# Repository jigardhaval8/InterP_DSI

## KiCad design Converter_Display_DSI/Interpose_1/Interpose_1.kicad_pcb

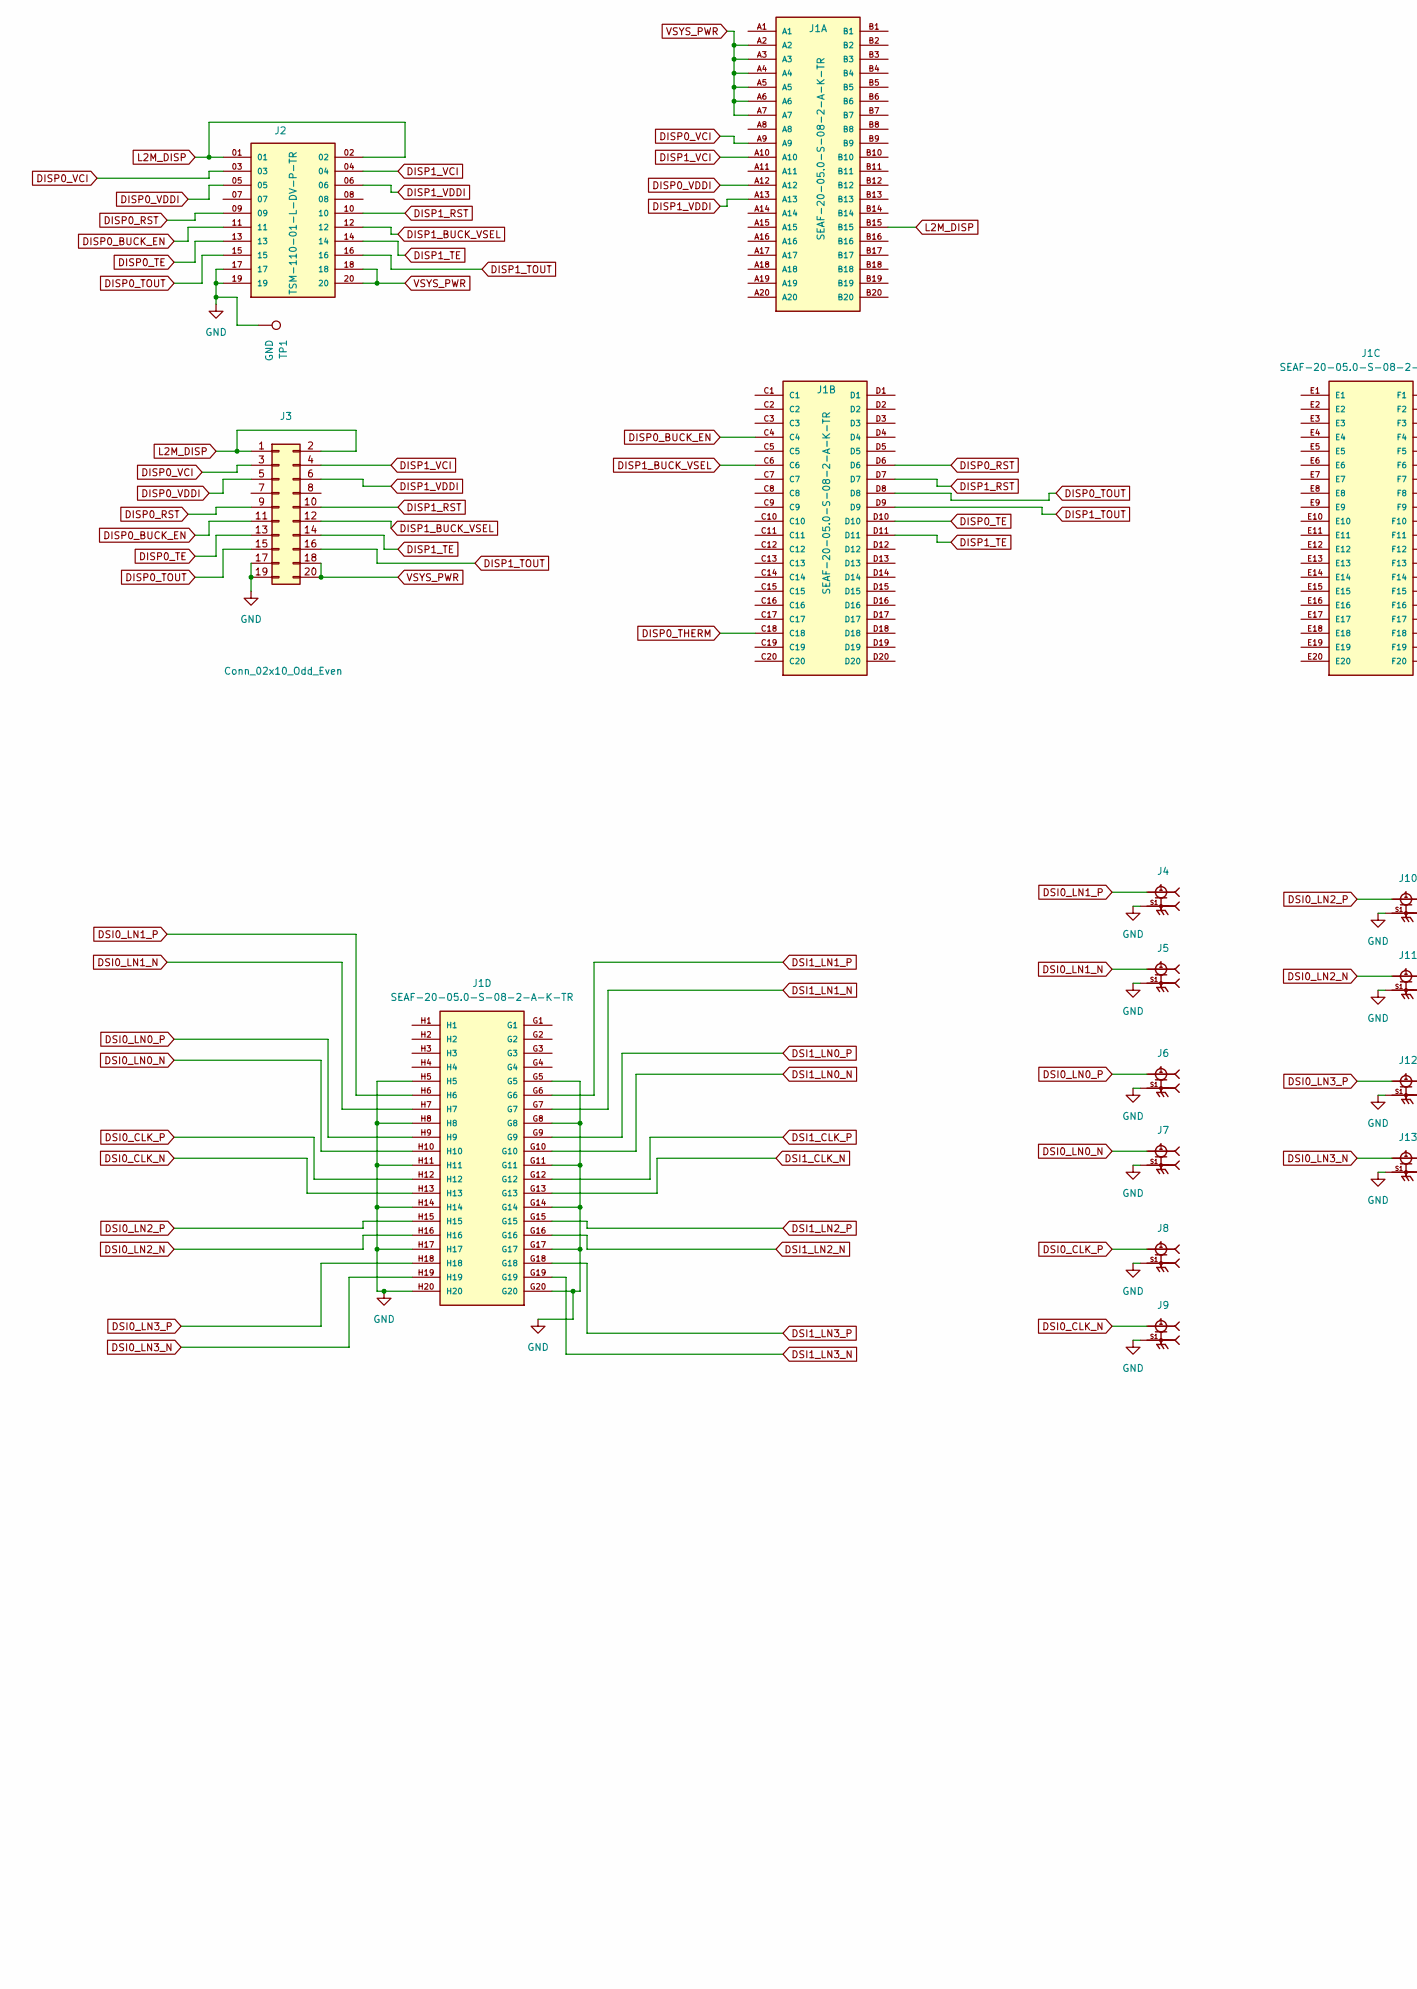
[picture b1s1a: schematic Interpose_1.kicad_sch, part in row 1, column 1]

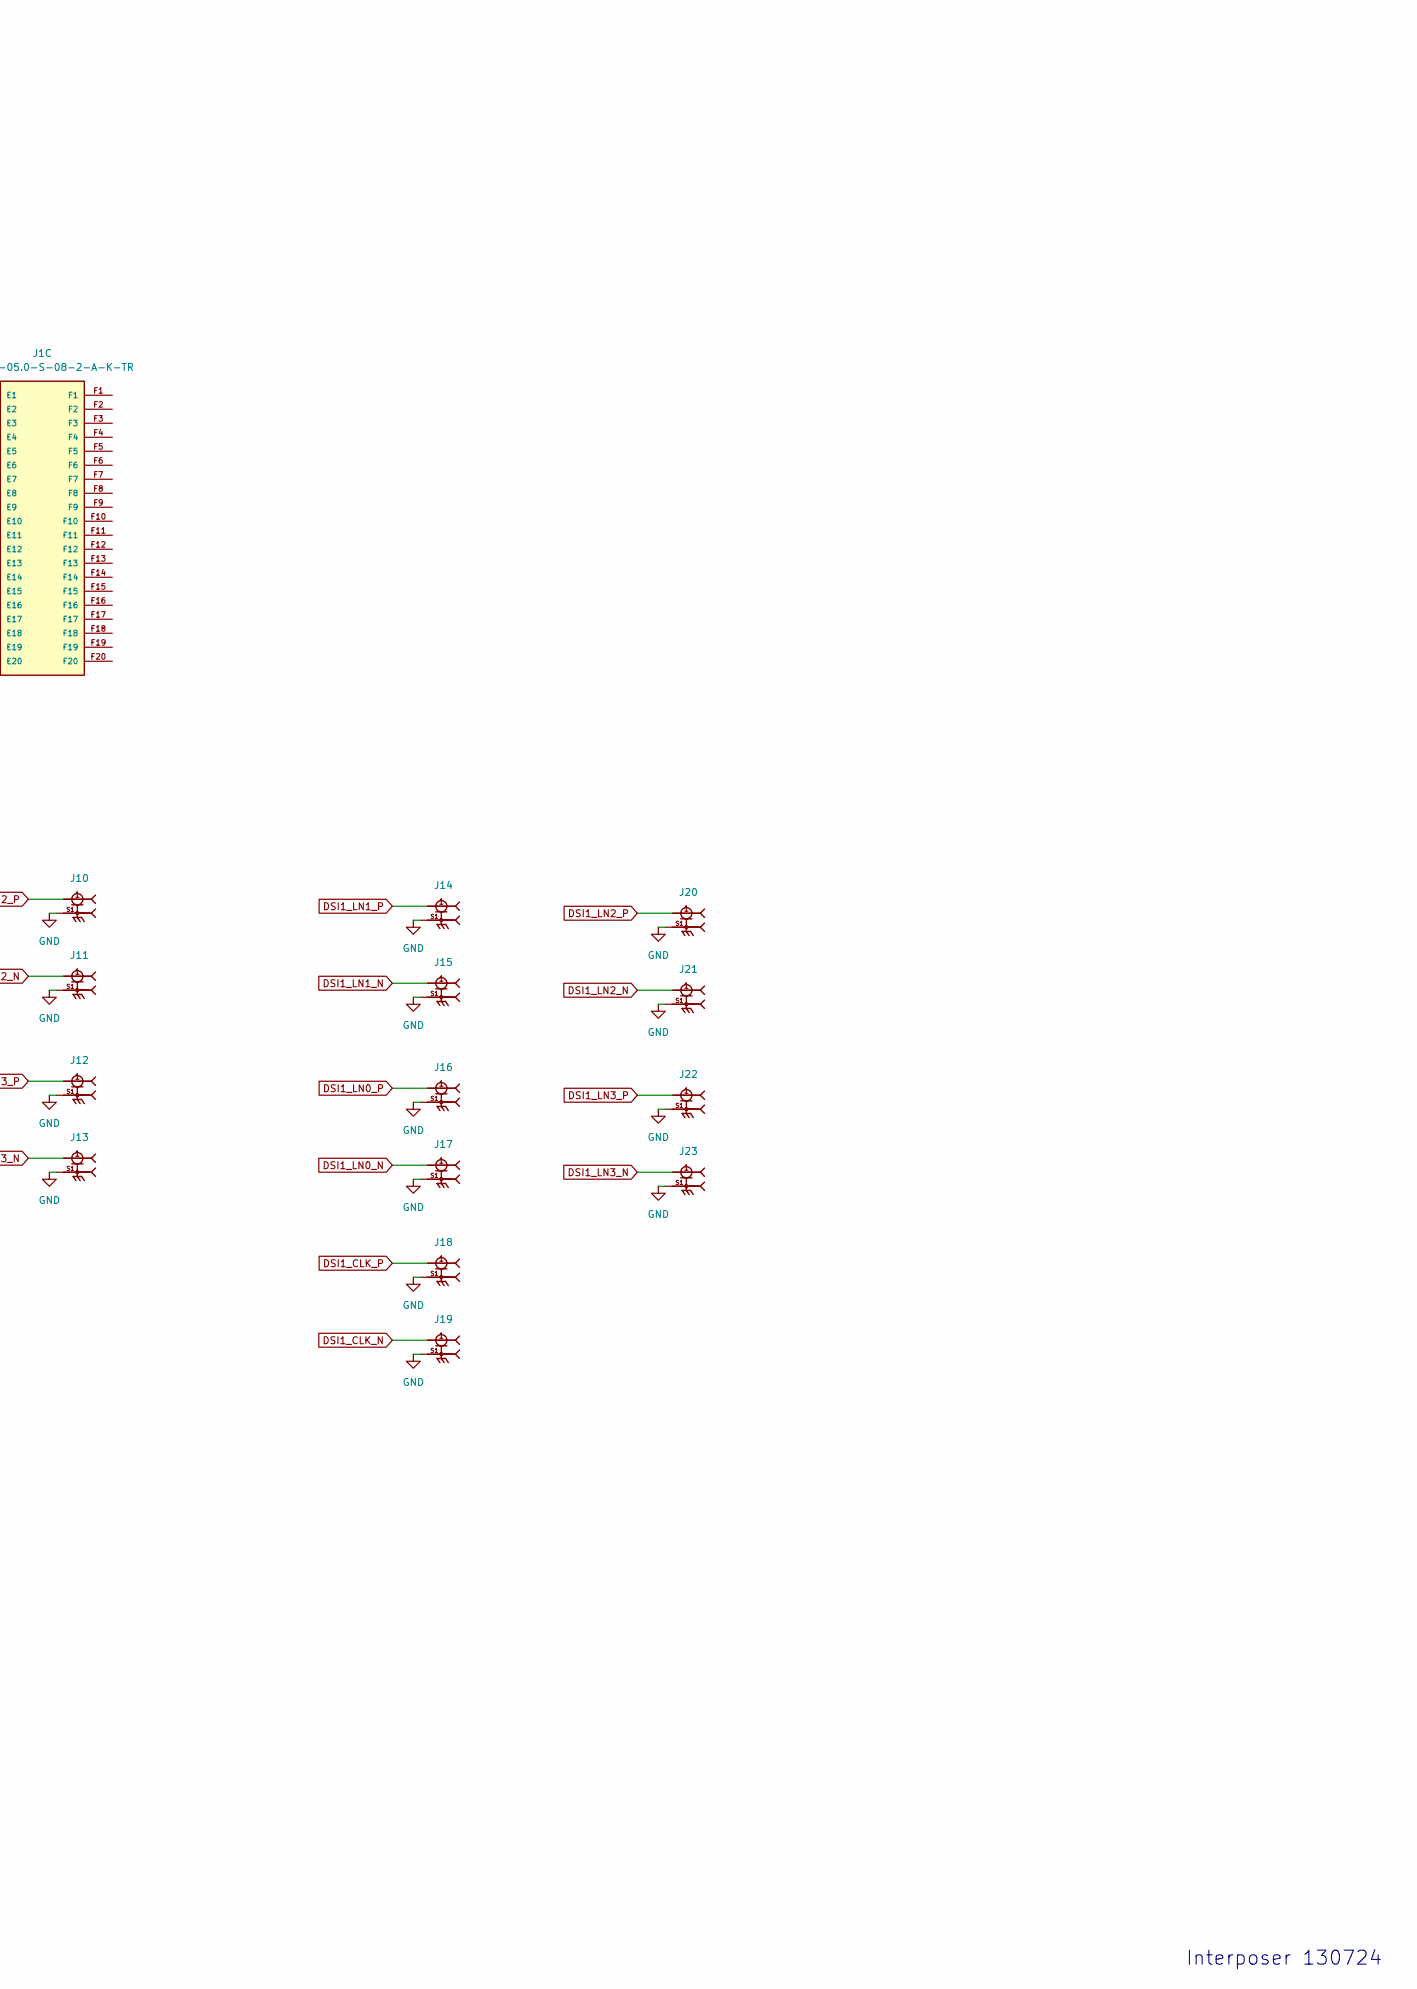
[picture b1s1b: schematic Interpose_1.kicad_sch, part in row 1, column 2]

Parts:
J1: SEAF-20-05.0-S-08-2-A-K-TR; SAMTEC_SEAF-20-05.0-S-08-2-A-K-TR
J2: TSM-110-01-L-DV-P-TR; SAMTEC_TSM-110-01-L-DV-P-TR
J3: Conn_02x10_Odd_Even; PinHeader_2x10_P2.54mm_Vertical
J4: DSI0_LN1_P; MOLEX_73251-1350; PARTREV C4
J5: DSI0_LN1_N; MOLEX_73251-1350; PARTREV C4
J6: DSI0_LN0_P; MOLEX_73251-1350; PARTREV C4
J7: DSI0_LN0_N; MOLEX_73251-1350; PARTREV C4
J8: DSI0_CLK_P; MOLEX_73251-1350; PARTREV C4
J9: DSI0_CLK_N; MOLEX_73251-1350; PARTREV C4
J10: DSI0_LN2_P; MOLEX_73251-1350; PARTREV C4
J11: DSI0_LN2_N; MOLEX_73251-1350; PARTREV C4
J12: DSI0_LN3_P; MOLEX_73251-1350; PARTREV C4
J13: DSI0_LN3_N; MOLEX_73251-1350; PARTREV C4
J14: DSI1_LN1_P; MOLEX_73251-1350; PARTREV C4
J15: DSI1_LN1_N; MOLEX_73251-1350; PARTREV C4
J16: DSI1_LN0_P; MOLEX_73251-1350; PARTREV C4
J17: DSI1_LN0_N; MOLEX_73251-1350; PARTREV C4
J18: DSI1_CLK_P; MOLEX_73251-1350; PARTREV C4
J19: DSI1_CLK_N; MOLEX_73251-1350; PARTREV C4
J20: DSI1_LN2_P; MOLEX_73251-1350; PARTREV C4
J21: DSI1_LN2_N; MOLEX_73251-1350; PARTREV C4
J22: DSI1_LN3_P; MOLEX_73251-1350; PARTREV C4
J23: DSI1_LN3_N; MOLEX_73251-1350; PARTREV C4
TP1: GND; TestPoint_THTPad_D1.5mm_Drill0.7mm

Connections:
DISP0_BUCK_EN: J1.C4, J2.11, J3.11
DISP0_RST: J1.D6, J2.09, J3.9
DISP0_TE: J1.D10, J2.13, J3.13
DISP0_THERM: J1.C18
DISP0_TOUT: J1.D8, J2.15, J3.15
DISP0_VCI: J1.A9, J2.03, J3.3
DISP0_VDDI: J1.A12, J2.05, J3.5
DISP1_BUCK_VSEL: J1.C6, J2.12, J3.12
DISP1_RST: J1.D7, J2.10, J3.10
DISP1_TE: J1.D11, J2.14, J3.14
DISP1_TOUT: J1.D9, J2.16, J3.16
DISP1_VCI: J1.A10, J2.04, J3.4
DISP1_VDDI: J1.A13, J2.06, J3.6
DSI0_CLK_N: J1.H13, J9.1
DSI0_CLK_P: J1.H12, J8.1
DSI0_LN0_N: J1.H10, J7.1
DSI0_LN0_P: J1.H9, J6.1
DSI0_LN1_N: J1.H7, J5.1
DSI0_LN1_P: J1.H6, J4.1
DSI0_LN2_N: J1.H16, J11.1
DSI0_LN2_P: J1.H15, J10.1
DSI0_LN3_N: J1.H19, J13.1
DSI0_LN3_P: J1.H18, J12.1
DSI1_CLK_N: J1.G13, J19.1
DSI1_CLK_P: J1.G12, J18.1
DSI1_LN0_N: J1.G10, J17.1
DSI1_LN0_P: J1.G9, J16.1
DSI1_LN1_N: J1.G7, J15.1
DSI1_LN1_P: J1.G6, J14.1
DSI1_LN2_N: J1.G16, J21.1
DSI1_LN2_P: J1.G15, J20.1
DSI1_LN3_N: J1.G19, J23.1
DSI1_LN3_P: J1.G18, J22.1
GND: J1.G5, J1.G8, J1.G11, J1.G14, J1.G17, J1.G20, J1.H5, J1.H8, J1.H11, J1.H14, J1.H17, J1.H20, J2.17, J2.19, J3.17, J3.19, J4.S1, J5.S1, J6.S1, J7.S1, J8.S1, J9.S1, J10.S1, J11.S1, J12.S1, J13.S1, J14.S1, J15.S1, J16.S1, J17.S1, J18.S1, J19.S1, J20.S1, J21.S1, J22.S1, J23.S1, TP1.1
L2M_DISP: J1.B15, J2.01, J2.02, J3.1, J3.2
VSYS_PWR: J1.A2, J1.A3, J1.A4, J1.A5, J1.A6, J1.A7, J2.18, J2.20, J3.18, J3.20

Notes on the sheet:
Interposer 130724

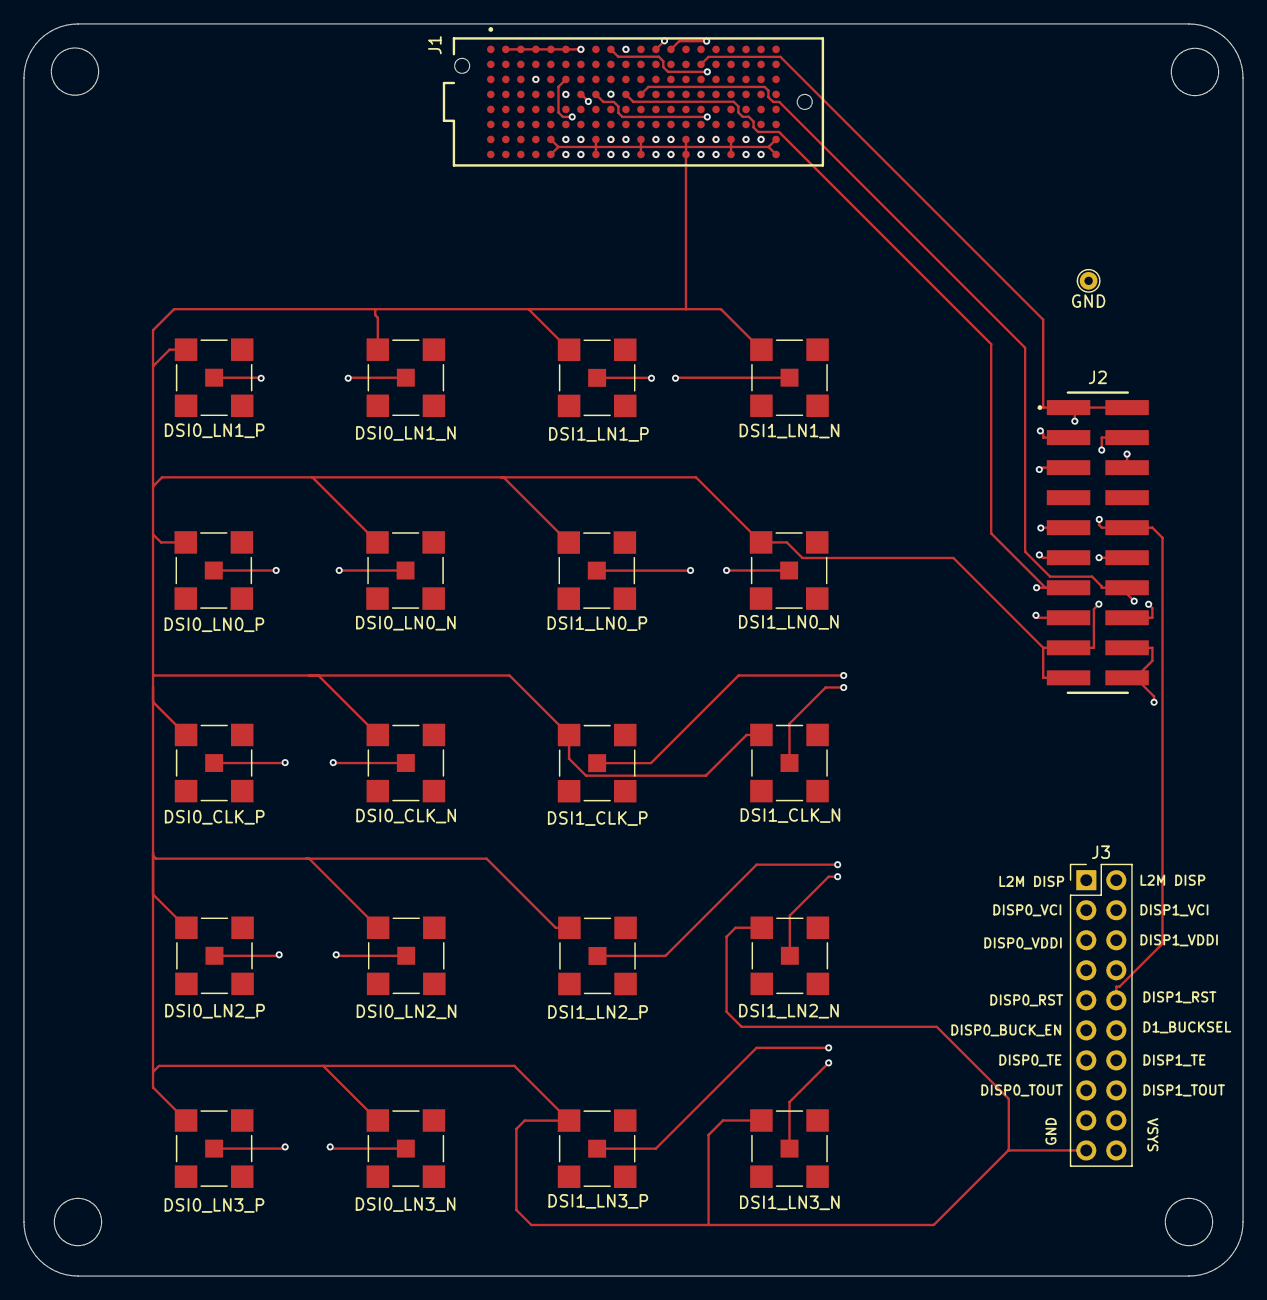
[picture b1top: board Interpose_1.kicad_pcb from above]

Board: 4 copper layers, 103.1 x 105.9 mm, 24 parts (0 on the bottom side), 35 nets.
